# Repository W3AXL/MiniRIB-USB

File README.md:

# MiniRIB-USB
USB-based Motorola RIB

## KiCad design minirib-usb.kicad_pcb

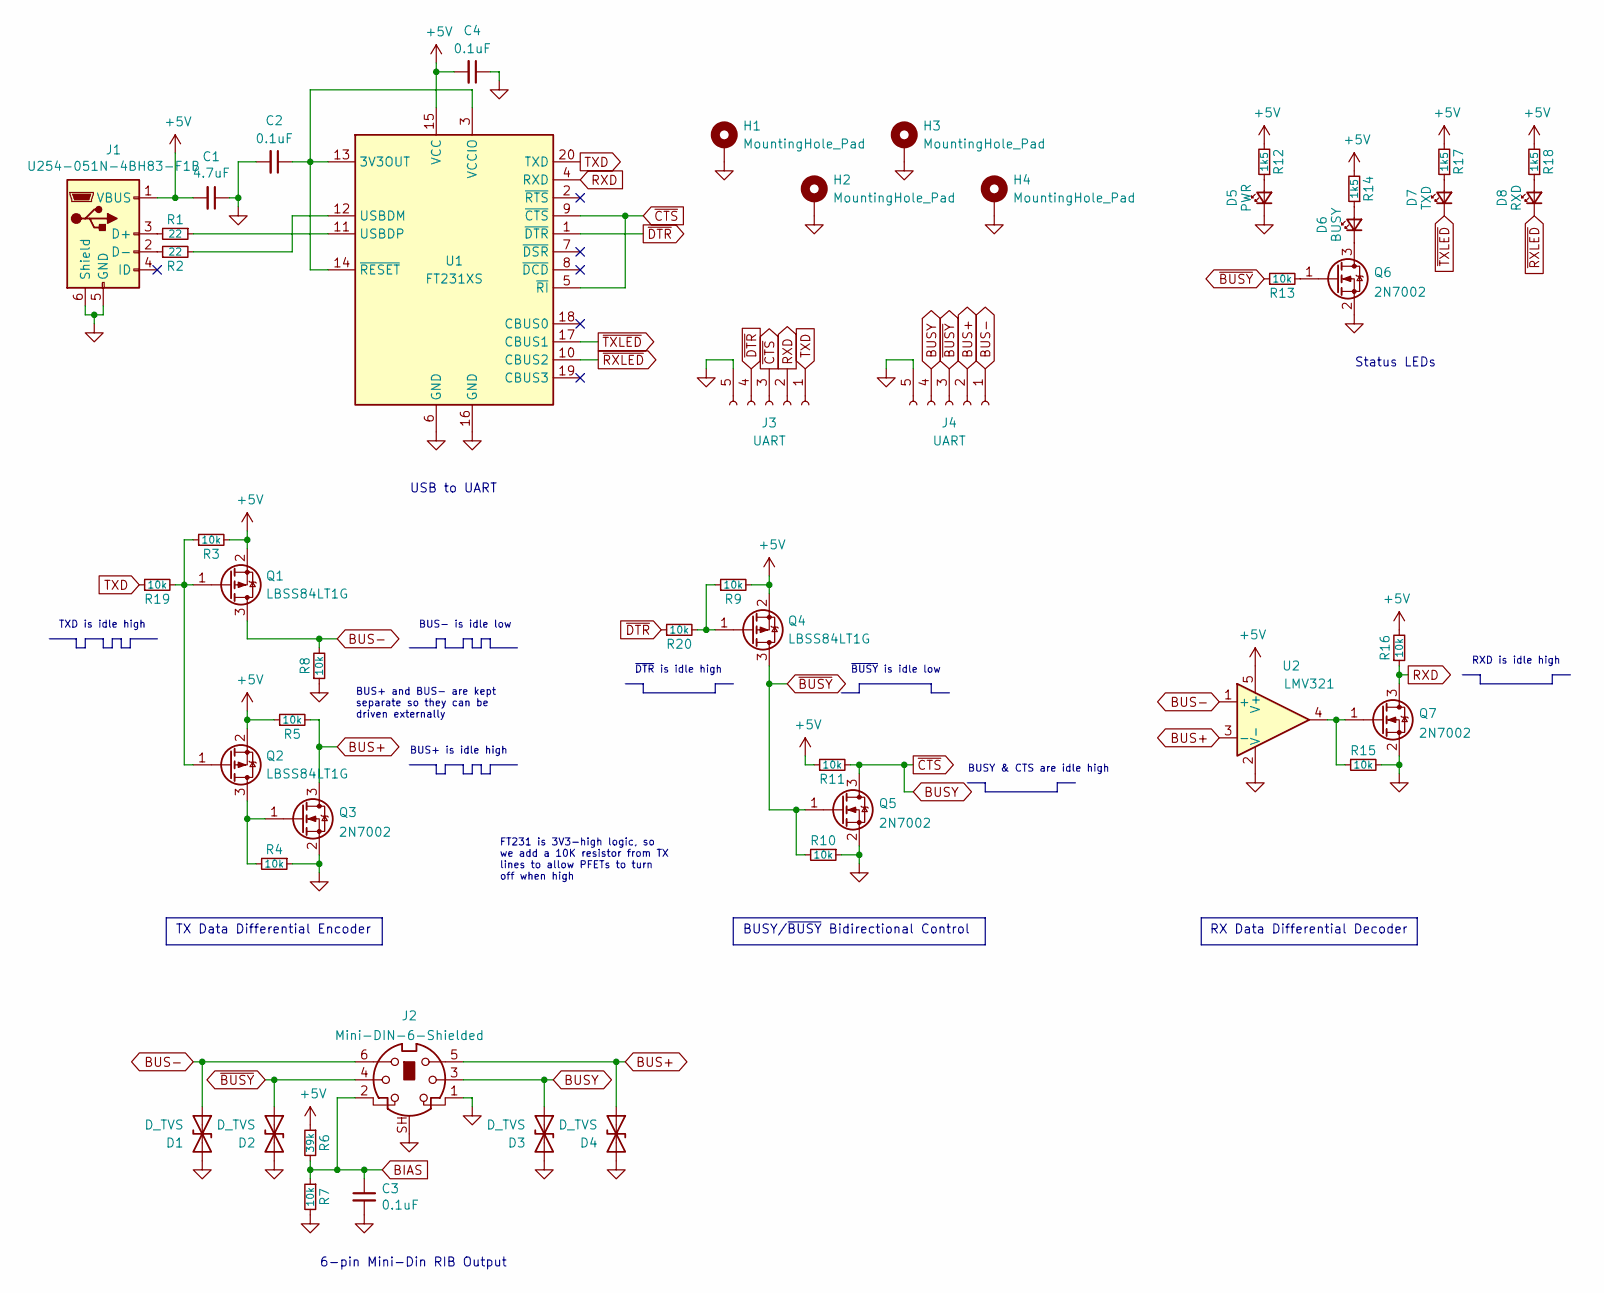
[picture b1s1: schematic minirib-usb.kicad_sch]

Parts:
C1: 4.7uF; C_0805_2012Metric_Pad1.18x1.45mm_HandSolder; LCSC C1779
C2, C3, C4: 0.1uF; C_0805_2012Metric_Pad1.18x1.45mm_HandSolder; LCSC C49678
D1, D2, D3, D4: D_TVS; D_SOD-123F; LCSC C2990473
D5: PWR; D_0805_2012Metric_Pad1.15x1.40mm_HandSolder; LCSC C434433
D6: BUSY; D_0805_2012Metric_Pad1.15x1.40mm_HandSolder; LCSC C2296
D7: TXD; D_0805_2012Metric_Pad1.15x1.40mm_HandSolder; LCSC C84256
D8: RXD; D_0805_2012Metric_Pad1.15x1.40mm_HandSolder; LCSC C434435
H1, H2, H3, H4: MountingHole_Pad; MountingHole_2.7mm_M2.5_Pad_TopBottom
J1: U254-051N-4BH83-F1B; LCSC C319169
J2: Mini-DIN-6-Shielded; KMDGX-6S-BS
J3, J4: UART; PinHeader_1x05_P2.54mm_Vertical
Q1, Q2, Q4: LBSS84LT1G; SOT-23_Handsoldering; LCSC C8492
Q3, Q5, Q6, Q7: 2N7002; SOT-23_Handsoldering; LCSC C8545
R1, R2: 22; R_0805_2012Metric_Pad1.20x1.40mm_HandSolder
R3, R4, R5, R7, R8, R9, R10, R11, R13, R15, R16, R19, R20: 10k; R_0805_2012Metric_Pad1.20x1.40mm_HandSolder; LCSC C17414
R6: 39k; R_0805_2012Metric_Pad1.20x1.40mm_HandSolder; LCSC C25826
R12, R14, R17, R18: 1k5; R_0805_2012Metric_Pad1.20x1.40mm_HandSolder; LCSC C4310
U1: FT231XS; SSOP-20_3.9x8.7mm_P0.635mm; LCSC C132160
U2: LMV321; SOT-23-5_HandSoldering; LCSC C7972

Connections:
+5V: C1.2, C4.2, J1.1 (VBUS), Q1.2 (S), Q2.2 (S), Q4.2 (S), R3.2, R5.1, R6.1, R9.2, R11.1, R12.2, R14.2, R16.2, R17.2, R18.2, U1.15 (VCC), U2.5 (V+)
BIAS: C3.1, J2.2, R6.2, R7.1
BUS+: D4.1 (A1), J2.5, J4.2, Q3.3 (D), R5.2, U2.3 (-)
BUS-: D1.1 (A1), J2.6, J4.1, Q1.3 (D), R8.2, U2.1 (+)
BUSY: D3.1 (A1), J2.3, J3.3, J4.4, Q5.3 (D), R11.2, U1.5 (~RI), U1.9 (~CTS)
GND: C1.1, C2.2, C3.2, C4.1, D1.2 (A2), D2.2 (A2), D3.2 (A2), D4.2 (A2), D5.1 (K), H1.1, H2.1, H3.1, H4.1, J1.5 (GND), J1.6 (Shield), J2.1, J2.SH, J3.5, J4.5, Q3.2 (S), Q5.2 (S), Q6.2 (S), Q7.2 (S), R4.1, R7.2, R8.1, R10.1, R15.2, U1.6 (GND), U1.16 (GND), U2.2 (V-)
unnamed: C2.1, U1.3 (VCCIO), U1.13 (3V3OUT), U1.14 (~RESET)
unnamed: D5.2 (A), R12.1
unnamed: D6.1 (K), Q6.3 (D)
unnamed: D6.2 (A), R14.1
unnamed: D7.2 (A), R17.1
unnamed: D8.2 (A), R18.1
unnamed: J1.2 (D-), R2.1
unnamed: J1.3 (D+), R1.2
unnamed: Q1.1 (G), Q2.1 (G), R3.1, R19.2
unnamed: Q2.3 (D), Q3.1 (G), R4.2
unnamed: Q4.1 (G), R9.1, R20.2
unnamed: Q6.1 (G), R13.2
unnamed: Q7.1 (G), R15.1, U2.4
unnamed: R1.1, U1.11 (USBDP)
unnamed: R2.2, U1.12 (USBDM)
RXD: J3.2, Q7.3 (D), R16.1, U1.4 (RXD)
TXD: J3.1, R19.1, U1.20 (TXD)
~BUSY: D2.1 (A1), J2.4, J4.3, Q4.3 (D), Q5.1 (G), R10.2, R13.1
~DTR: J3.4, R20.1, U1.1 (~DTR)
~RXLED: D8.1 (K), U1.10 (CBUS2)
~TXLED: D7.1 (K), U1.17 (CBUS1)

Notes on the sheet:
Status LEDs
FT231 is 3V3-high logic, so we add a 10K resistor from TX lines to allow PFETs to turn off when high
BUS- is idle low
TX Data Differential Encoder
BUSY & CTS are idle high
RX Data Differential Decoder
~{BUSY} is idle low
6-pin Mini-Din RIB Output
~{DTR} is idle high
BUSY/~{BUSY} Bidirectional Control
RXD is idle high
TXD is idle high
USB to UART
BUS+ is idle high
BUS+ and BUS- are kept separate so they can be driven externally

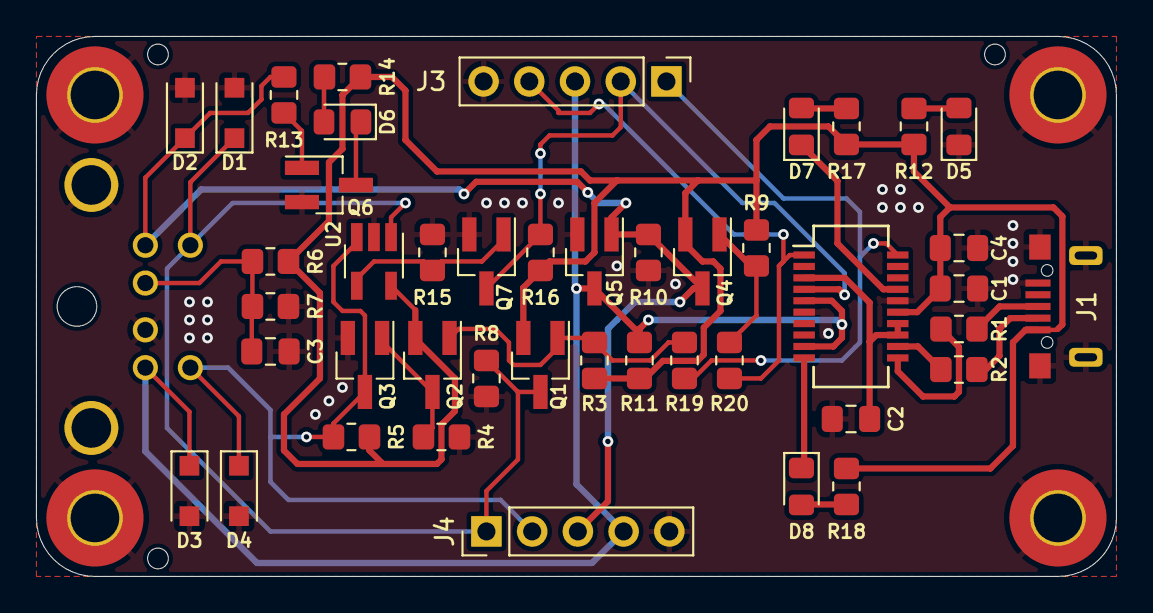
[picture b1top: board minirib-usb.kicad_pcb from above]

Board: 2 copper layers, 60.0 x 30.0 mm, 52 parts (0 on the bottom side), 27 nets.

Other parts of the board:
th1, th2, th3: tooling-hole

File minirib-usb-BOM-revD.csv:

"Source:","H:\Documents\GitHub\MiniRIB-USB\minirib-usb.kicad_sch"
"Date:","4/5/2023 10:20:10 AM"
"Tool:","Eeschema (6.0.7)"
"Generator:","C:\Program Files\KiCad\6.0\bin\scripting\plugins/bom_csv_grouped_by_value_with_fp.py"
"Component Count:","47"
"Ref","Qnty","Value","Cmp name","Footprint","Description","Vendor"
"C1, ","1","4.7uF","C_Small","Capacitor_SMD:C_0805_2012Metric_Pad1.18x1.45mm_HandSolder","Unpolarized capacitor, small symbol",""
"C2, C4, ","2","0.1uF","C_Small","Capacitor_SMD:C_0805_2012Metric_Pad1.18x1.45mm_HandSolder","Unpolarized capacitor, small symbol",""
"C3, ","1","220pF","C_Small","Capacitor_SMD:C_0805_2012Metric_Pad1.18x1.45mm_HandSolder","Unpolarized capacitor, small symbol",""
"D1, D2, D3, D4, ","4","D_TVS","D_TVS","Diode_SMD:D_0805_2012Metric_Pad1.15x1.40mm_HandSolder","Bidirectional transient-voltage-suppression diode",""
"D5, ","1","PWR","LED_Small","Diode_SMD:D_0805_2012Metric_Pad1.15x1.40mm_HandSolder","Light emitting diode, small symbol",""
"D6, ","1","BUSY","LED_Small","Diode_SMD:D_0805_2012Metric_Pad1.15x1.40mm_HandSolder","Light emitting diode, small symbol",""
"D7, ","1","TXD","LED_Small","Diode_SMD:D_0805_2012Metric_Pad1.15x1.40mm_HandSolder","Light emitting diode, small symbol",""
"D8, ","1","RXD","LED_Small","Diode_SMD:D_0805_2012Metric_Pad1.15x1.40mm_HandSolder","Light emitting diode, small symbol",""
"H1, H2, H3, H4, ","4","MountingHole_Pad","MountingHole_Pad","MountingHole:MountingHole_2.7mm_M2.5_Pad_TopBottom","Mounting Hole with connection",""
"J1, ","1","USB_B_Micro","USB_B_Micro","Connector_USB:USB_Micro-B_Wuerth_629105150521","USB Micro Type B connector",""
"J2, ","1","Mini-DIN-6-Shielded","Mini-DIN-6-Shielded","MiniRIB-USB:KMDGX-6S-BS","6-pin Mini-DIN connector",""
"J3, J4, ","2","UART","Conn_01x05_Female","Connector_PinHeader_2.54mm:PinHeader_1x05_P2.54mm_Vertical","Generic connector, single row, 01x05, script generated (kicad-library-utils/schlib/autogen/connector/)",""
"Q1, Q2, Q4, ","3","BS84W","Q_PMOS_GSD","Package_TO_SOT_SMD:SOT-323_SC-70_Handsoldering","P-MOSFET transistor, gate/source/drain",""
"Q3, Q5, Q6, Q7, ","4","BSS138W","Q_NMOS_GSD","Package_TO_SOT_SMD:SOT-323_SC-70_Handsoldering","N-MOSFET transistor, gate/source/drain",""
"R1, R2, ","2","22","R_Small","Resistor_SMD:R_0805_2012Metric_Pad1.20x1.40mm_HandSolder","Resistor, small symbol",""
"R3, R4, R5, R7, R8, R9, R10, R11, R13, R15, R16, ","11","10k","R_Small","Resistor_SMD:R_0805_2012Metric_Pad1.20x1.40mm_HandSolder","Resistor, small symbol",""
"R6, ","1","39k","R_Small","Resistor_SMD:R_0805_2012Metric_Pad1.20x1.40mm_HandSolder","Resistor, small symbol",""
"R12, R14, R17, R18, ","4","1k5","R_Small","Resistor_SMD:R_0805_2012Metric_Pad1.20x1.40mm_HandSolder","Resistor, small symbol",""
"U1, ","1","FT231XS","FT231XS","Package_SO:SSOP-20_3.9x8.7mm_P0.635mm","Full Speed USB to Full Handshake UART, SSOP-20",""
"U2, ","1","TL071","TL071","Package_TO_SOT_SMD:SOT-23-5_HandSoldering","Single Low-Noise JFET-Input Operational Amplifiers, DIP-8/SOIC-8",""

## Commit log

2021-07-26 initial schematic work
2021-08-07 added test connector
2021-08-07 schematic rework
    more closely following the original RIB schematic
2021-09-13 updated schematic with test headers and cleaned up
2021-09-14 finalized initial schematic work
2021-12-09 more work on schematic and PCB
2021-12-10 Finalized rev A schematic and PCB
2021-12-10 extra schematic work
2021-12-11 finalized schematic for real this time
2021-12-11 generated gerbers
2022-01-04 converted to Kicad 6 project
2022-01-04 finalized schematic for rev B
    switched to CH340G for USB to serial operations due to supply chain issues with FTDI, and re-worked BUS- and /BUSY transistor arrangements to work properly without +15V RS232 as found in original sch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
2022-01-04 started work on PCB, added LTSpice sims for circuit
2022-01-04 finalized PCB & schematic for rev B
2022-01-04 switched to SC70 package for TL081
2022-01-04 added new BOM for rev B and cleaned up kicad v5 files
2022-01-04 updated gerbers and new schematic pdf
2022-01-04 small PCB cleanup
    fixed PCB text and added logo
2022-01-04 added drill files to gerbers
2022-01-04 added correct capacitors for crystal
2022-01-21 schematic fixes based on rev B testing
    - switched Opamp to MCP6491T to use correct footprint (SC70 footprint for TL081H is incorrect)
    - Removed D7 BUSY LED as it was interfering with the proper signalling on the BUSY line
2022-01-21 Updated sim & project file
2022-01-28 Update RIB Signals.txt
    Clarified RIB signals based on observation of real RIB behavior. Realized that UART TX/RX is active high while RS232 is active low. Will need to rework schematic & pcb
2022-05-05 rev C total redesign
    Changed circuit to use an FT231 + MAX232 usb chain, with original transistor logic conversion identical to the RLN4008B schematic to ensure proper operation
2022-10-10 finalized schematic and pcb
2022-10-12 generated schematic and gerbers for rev C PCB
2023-03-29 initial revision D updates
2023-04-03 finalizing rev D
2023-04-12 revision E updates
    added 10k resistors to TX & DTR lines from FT231XS to allow PFETs to turn off properly when TX/DTR at 3V3. Currently they're always on (oops)
2023-04-18 PCB assembly updates
    updates to revision E to add LCSC components to allow for JLCPCB manufacture
2023-05-07 finalized schematic and layout for production
2023-07-25 updated gitignore
2023-07-25 removed unneeded gerbers
